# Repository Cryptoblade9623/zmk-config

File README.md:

Introduction
This is an ergonomic split keyboard that I designed to match the shape of my hands.
It is designed this way to hopefully reduce strain on my wrists and hands when typing.
I like making stuff.
I also just think that split keyboards are cool.
It uses the Seeeduino XIAO BLE nRF52840.
It has bluetooth communication capabilities and has a USB-C port.

Images

Above is my Split keyboard design on Fusion360.

Above is my PCB design.

Above is the root sheet for the schematics.

Above are the left then right schematics sheets.

Status
I have designed everything (hopefully) like the firmware, PCB and schematics.
I have also created the BOM.
I will start assembly when it is approved and i buy the parts needed.

Assembly instructions
1. Solder the diodes and hall sensors.
2. Solder the male header pins onto the seeeduino.
3. Link the seeeduino to the firmware on ZMK.
4. Solder the other side of the male header pins onto the PCB.
5. Screw the stabilizers into the PCB.
6. Solder the wires of the battery to the bat pins of the microcontroller and the sliding switch.
7. Place the battery into the small cavity in between the case and where the PCb is meant to go.
8. Screw the sliding switch into the side.
9. Insert the brass threaded insert into the 3d printed case in the middle and on the rim by heating the inserts and pushing them in.
10. Screw in the five mounting screw in to the middle.
11. Place the PCB on top and screw the black screws in.
12. Glue the magnets into the holes in the 3d printed case.
13. Click the key Switches into the plate.
14. Screw the plate on the bigger portion of the case.
15. Click the keycaps into place.
16. Repeat for both halves.
17. Pair both the halves together.
18. Test the keyboard.
I have not actually built the keyboard yet.

BOM
Name	                     Purpose	                          Units Total	            Total (USD)    	Distributor
Male header pin row        For soldering Seeeduino to PCB    	1     	                $1.31	          AliExpress
Battery	                   To supply power                   	1	Pair                  $9.18	          AliExpress
Screws                   	 Secure keyboard parts	            1 Pack	                $1.31	          AliExpress
Mounting screws	           Secure PCB in place	              1 Pack	                $0.74	          AliExpress
Threaded insert	           Housing for screws               	1 Pack                	$1.64	          AliExpress
PCB	                       Main circuit board               	1 Pack                	$14.38	        JLCPCB
Diodes	                   Direct current one way            	1 Pack	                $5.57	          AliExpress
Hall sensors	             Magnetic detection 	              3 Packs	                $11.51   	      AliExpress
Magnets                    Connect halves together	          1 Pack                	$1.31         	AliExpress
Sliding Switches           Power On/Off                     	1	Pack                  $5.10          	Amazon
Stabilizers                Support for larger keycaps	        2	                      $4.44	          AliExpress
Key Switches	             Register key strokes	              1 Pack                	$45.27         	AliExpress
Seeeduino (2pcs)         	 Main controllers	                  1 Pair	                $38.42        	AliExpress
Keycaps	                   Key labels	                        1 Set                 	$16.79	        AliExpress

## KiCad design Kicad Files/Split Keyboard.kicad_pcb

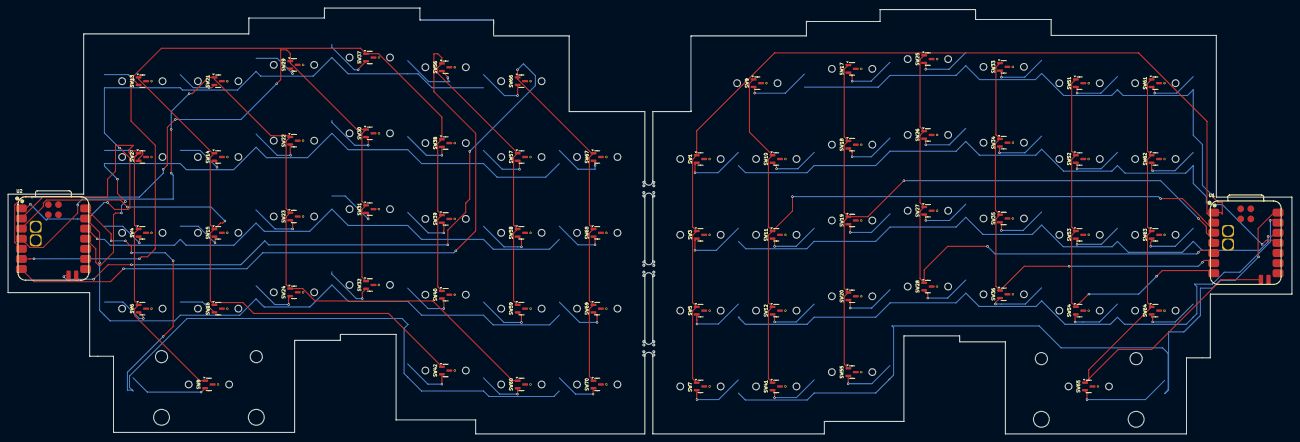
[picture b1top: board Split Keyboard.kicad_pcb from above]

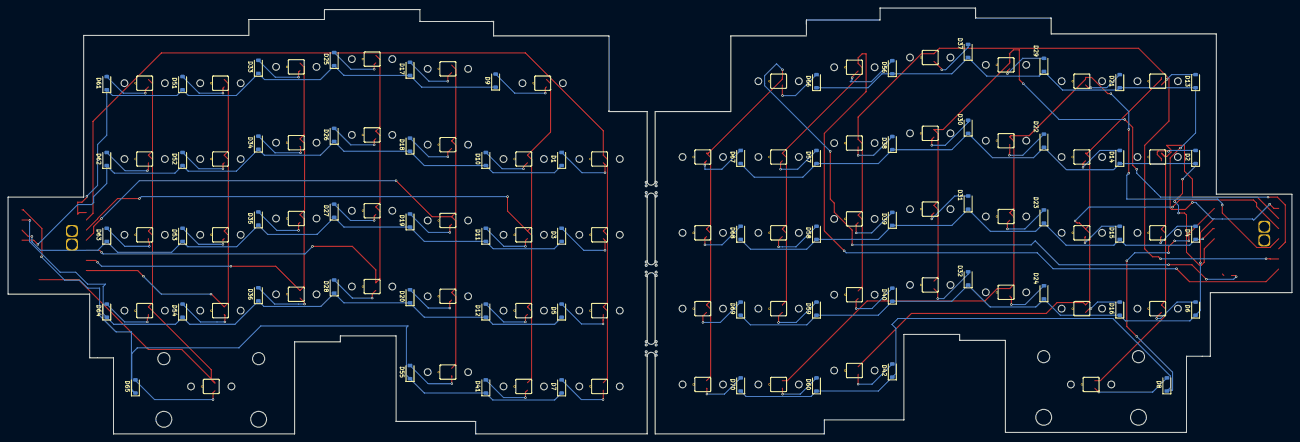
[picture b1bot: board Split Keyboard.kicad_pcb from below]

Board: 2 copper layers, 322.5 x 106.9 mm, 131 parts (62 on the bottom side), 87 nets.

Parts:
D1, D2, D3, D4, D5, D6, D7, D8, D9, D10, D11, D12, D13, D14, D15, D16, D17, D18, D19, D20, D21, D22, D23, D24, D25, D26, D27, D28, D29, D30, D31, D32, D33, D34, D35, D36, D37, D38, D39, D40, D41, D42, D51, D52, D53, D54, D55, D56, D57, D58, D59, D60, D61, D62, D63, D64, D65, D66, D67, D68, D69, D70: D; D_SOD-123
H1, H3, H5: MountingHole; MouseBite-Slot_2.0x2.0mm_inset_D0.5mm_P0.85mm_4h_Trace
S1, S2: MX_stab; STAB_MX_2u
SW1, SW2, SW3, SW4, SW5, SW6, SW7, SW8, SW10, SW11, SW12, SW14, SW15, SW16, SW17, SW18, SW19, SW20, SW21, SW22, SW23, SW24, SW25, SW26, SW27, SW28, SW29, SW30, SW31, SW32, SW33, SW34, SW35, SW36, SW37, SW38, SW39, SW40, SW41, SW42, SW51, SW52, SW53, SW54, SW55, SW56, SW57, SW58, SW59, SW60, SW61, SW62, SW63, SW64, SW65, SW66, SW67, SW68, SW69, SW70: SW_Push; SW_MX_HE_0deg_1u
SW9, SW13: SW_Push; SW_MX_HE_0deg_1.5u
U1, U2: Seeeduino Xiao nRF52840; modified-XIAO-nRF52840-SMD

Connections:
/Left/COL0: SW1.1, SW3.1, SW5.1, SW7.1, U1.2 (P0.03)
/Left/COL1: SW9.1, SW10.1, SW11.1, SW12.1, SW41.1, U1.3 (P0.28)
/Left/COL2: SW17.1, SW18.1, SW19.1, SW20.1, SW55.1, U1.4 (P0.29)
/Left/COL3: SW25.1, SW26.1, SW27.1, SW28.1, U1.5 (P0.04)
/Left/COL4: SW33.1, SW34.1, SW35.1, SW36.1, U1.6 (P0.05)
/Left/COL5: SW51.1, SW52.1, SW53.1, SW54.1, U1.7 (P1.11)
/Left/COL6: SW61.1, SW62.1, SW63.1, SW64.1, SW65.1, U1.17 (P0.09)
/Left/ROW0: D9.1 (K), D17.1 (K), D25.1 (K), D33.1 (K), D51.1 (K), D61.1 (K), U1.1 (P0.02)
/Left/ROW1: D1.1 (K), D10.1 (K), D18.1 (K), D26.1 (K), D34.1 (K), D52.1 (K), D62.1 (K), U1.11 (P1.15)
/Left/ROW2: D3.1 (K), D11.1 (K), D19.1 (K), D27.1 (K), D35.1 (K), D53.1 (K), D63.1 (K), U1.12 (P1.14)
/Left/ROW3: D5.1 (K), D12.1 (K), D20.1 (K), D28.1 (K), D36.1 (K), D54.1 (K), D64.1 (K), U1.13 (P1.13)
/Left/ROW4: D7.1 (K), D41.1 (K), D55.1 (K), D65.1 (K), U1.14 (P1.12)
/Right/COL0: SW2.1, SW4.1, SW6.1, SW8.1, U2.2 (P0.03)
/Right/COL1: SW13.1, SW14.1, SW15.1, SW16.1, SW42.1, U2.3 (P0.28)
/Right/COL2: SW21.1, SW22.1, SW23.1, SW24.1, SW60.1, U2.4 (P0.29)
/Right/COL3: SW29.1, SW30.1, SW31.1, SW32.1, U2.5 (P0.04)
/Right/COL4: SW37.1, SW38.1, SW39.1, SW40.1, U2.6 (P0.05)
/Right/COL5: SW56.1, SW57.1, SW58.1, SW59.1, U2.7 (P1.11)
/Right/COL6: SW66.1, SW67.1, SW68.1, SW69.1, SW70.1, U2.17 (P0.09)
/Right/ROW0: D13.1 (K), D21.1 (K), D29.1 (K), D37.1 (K), D56.1 (K), D66.1 (K), U2.1 (P0.02)
/Right/ROW1: D2.1 (K), D14.1 (K), D22.1 (K), D30.1 (K), D38.1 (K), D57.1 (K), D67.1 (K), U2.11 (P1.15)
/Right/ROW2: D4.1 (K), D15.1 (K), D23.1 (K), D31.1 (K), D39.1 (K), D58.1 (K), D68.1 (K), U2.12 (P1.14)
/Right/ROW3: D6.1 (K), D16.1 (K), D24.1 (K), D32.1 (K), D40.1 (K), D59.1 (K), D69.1 (K), U2.13 (P1.13)
/Right/ROW4: D8.1 (K), D42.1 (K), D60.1 (K), D70.1 (K), U2.14 (P1.12)
GND: U1.9 (GND), U2.9 (GND)
unnamed: D1.2 (A), SW1.2
unnamed: D2.2 (A), SW2.2
unnamed: D3.2 (A), SW3.2
unnamed: D4.2 (A), SW4.2
unnamed: D5.2 (A), SW5.2
unnamed: D6.2 (A), SW6.2
unnamed: D7.2 (A), SW7.2
unnamed: D8.2 (A), SW8.2
unnamed: D9.2 (A), SW9.2
unnamed: D10.2 (A), SW10.2
unnamed: D11.2 (A), SW11.2
unnamed: D12.2 (A), SW12.2
unnamed: D13.2 (A), SW13.2
unnamed: D14.2 (A), SW14.2
unnamed: D15.2 (A), SW15.2
unnamed: D16.2 (A), SW16.2
unnamed: D17.2 (A), SW17.2
unnamed: D18.2 (A), SW18.2
unnamed: D19.2 (A), SW19.2
unnamed: D20.2 (A), SW20.2
unnamed: D21.2 (A), SW21.2
unnamed: D22.2 (A), SW22.2
unnamed: D23.2 (A), SW23.2
unnamed: D24.2 (A), SW24.2
unnamed: D25.2 (A), SW25.2
unnamed: D26.2 (A), SW26.2
unnamed: D27.2 (A), SW27.2
unnamed: D28.2 (A), SW28.2
unnamed: D29.2 (A), SW29.2
unnamed: D30.2 (A), SW30.2
unnamed: D31.2 (A), SW31.2
unnamed: D32.2 (A), SW32.2
unnamed: D33.2 (A), SW33.2
unnamed: D34.2 (A), SW34.2
unnamed: D35.2 (A), SW35.2
unnamed: D36.2 (A), SW36.2
unnamed: D37.2 (A), SW37.2
unnamed: D38.2 (A), SW38.2
unnamed: D39.2 (A), SW39.2
unnamed: D40.2 (A), SW40.2
unnamed: D41.2 (A), SW41.2
unnamed: D42.2 (A), SW42.2
unnamed: D51.2 (A), SW51.2
unnamed: D52.2 (A), SW52.2
unnamed: D53.2 (A), SW53.2
unnamed: D54.2 (A), SW54.2
unnamed: D55.2 (A), SW55.2
unnamed: D56.2 (A), SW56.2
unnamed: D57.2 (A), SW57.2
unnamed: D58.2 (A), SW58.2
unnamed: D59.2 (A), SW59.2
unnamed: D60.2 (A), SW60.2
unnamed: D61.2 (A), SW61.2
unnamed: D62.2 (A), SW62.2
unnamed: D63.2 (A), SW63.2
unnamed: D64.2 (A), SW64.2
unnamed: D65.2 (A), SW65.2
unnamed: D66.2 (A), SW66.2
unnamed: D67.2 (A), SW67.2
unnamed: D68.2 (A), SW68.2
unnamed: D69.2 (A), SW69.2
unnamed: D70.2 (A), SW70.2

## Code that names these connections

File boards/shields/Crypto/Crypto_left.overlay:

/ {
    chosen {
        zmk,kscan = &kscan0;
    };

    kscan0: kscan {
        compatible = "zmk,kscan-gpio-matrix";
        wakeup-source;
        diode-direction = "col2row";

        col-gpios
            = <&xiao_d 1 GPIO_ACTIVE_HIGH> // COL0 (Pad 2)
            , <&xiao_d 2 GPIO_ACTIVE_HIGH> // COL1 (Pad 3)
            , <&xiao_d 3 GPIO_ACTIVE_HIGH> // COL2 (Pad 4)
            , <&xiao_d 4 GPIO_ACTIVE_HIGH> // COL3 (Pad 5)
            , <&xiao_d 5 GPIO_ACTIVE_HIGH> // COL4 (Pad 6)
            , <&xiao_d 6 GPIO_ACTIVE_HIGH> // COL5 (Pad 7)
            , <&gpio0 9 GPIO_ACTIVE_HIGH>  // COL6 (Pad 17 - The "Secret" 12th pin)
            ;

        row-gpios
            = <&xiao_d 0  (GPIO_ACTIVE_HIGH | GPIO_PULL_DOWN)> // ROW0 (Pad 1)
            , <&xiao_d 7  (GPIO_ACTIVE_HIGH | GPIO_PULL_DOWN)> // ROW1 (Pad 11)
            , <&xiao_d 8  (GPIO_ACTIVE_HIGH | GPIO_PULL_DOWN)> // ROW2 (Pad 12)
            , <&xiao_d 9  (GPIO_ACTIVE_HIGH | GPIO_PULL_DOWN)> // ROW3 (Pad 13)
            , <&xiao_d 10 (GPIO_ACTIVE_HIGH | GPIO_PULL_DOWN)> // ROW4 (Pad 14)
            ;
    };
};

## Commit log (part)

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2026-03-21 Crypto
2026-03-22 Final Keymap
2026-03-22 Rename Crypto,keymap to Crypto.keymap
2026-03-22 Create Schematics
2026-03-30 Rename config/west.yml to west.yml
2026-03-30 Rename config/Crypto.keymap to Crypto.keymap
2026-03-30 Rename config/seeeduino_xiao_ble.conf to seeeduino_xiao_ble.conf
2026-03-30 Rename seeeduino_xiao_ble.conf to Crypto.conf
2026-03-30 Rename Crypto.conf to config/Crypto.conf
2026-03-30 Rename Crypto.keymap to config/Crypto.keymap
2026-03-30 Rename west.yml to config/west.yml
2026-03-30 Rename Split Keyboard-all-pos.csv to BOM/Split Keyboard-all-pos.csv
2026-03-30 Rename Split Keyboard-bottom-pos.csv to BOM/Split Keyboard-bottom-pos.csv
2026-03-30 Rename Split Keyboard-top-pos.csv to BOM/lit Keyboard-top-pos.csv
2026-03-30 Rename lit Keyboard-top-pos.csv to Split Keyboard-top-pos.csv
2026-03-30 Rename Split Keyboard.csv to BOM/Split Keyboard.csv
2026-03-30 Rename Screenshot 2026-03-22 103136.png to Amazon cart
2026-03-30 Create Seeeduino
2026-03-30 Create Marbastlib
2026-03-30 Create something
2026-03-30 Create some
2026-03-30 Create Footprints
2026-03-30 Create Keys
2026-03-30 Create xiao
2026-03-30 Create slots
2026-03-30 Create Masrdjfbs;f
2026-03-30 Rename XIAO-nRF52840-SMD.kicad_mod to XIAO-nRF52840-SMD.kicad_mod
2026-03-30 Create key
2026-03-30 Create a
2026-03-30 Rename Switch.kicad_sym to Switch.kicad_sym
2026-03-30 Create d
2026-03-30 Create s
2026-03-30 Create h
2026-03-30 Create m
